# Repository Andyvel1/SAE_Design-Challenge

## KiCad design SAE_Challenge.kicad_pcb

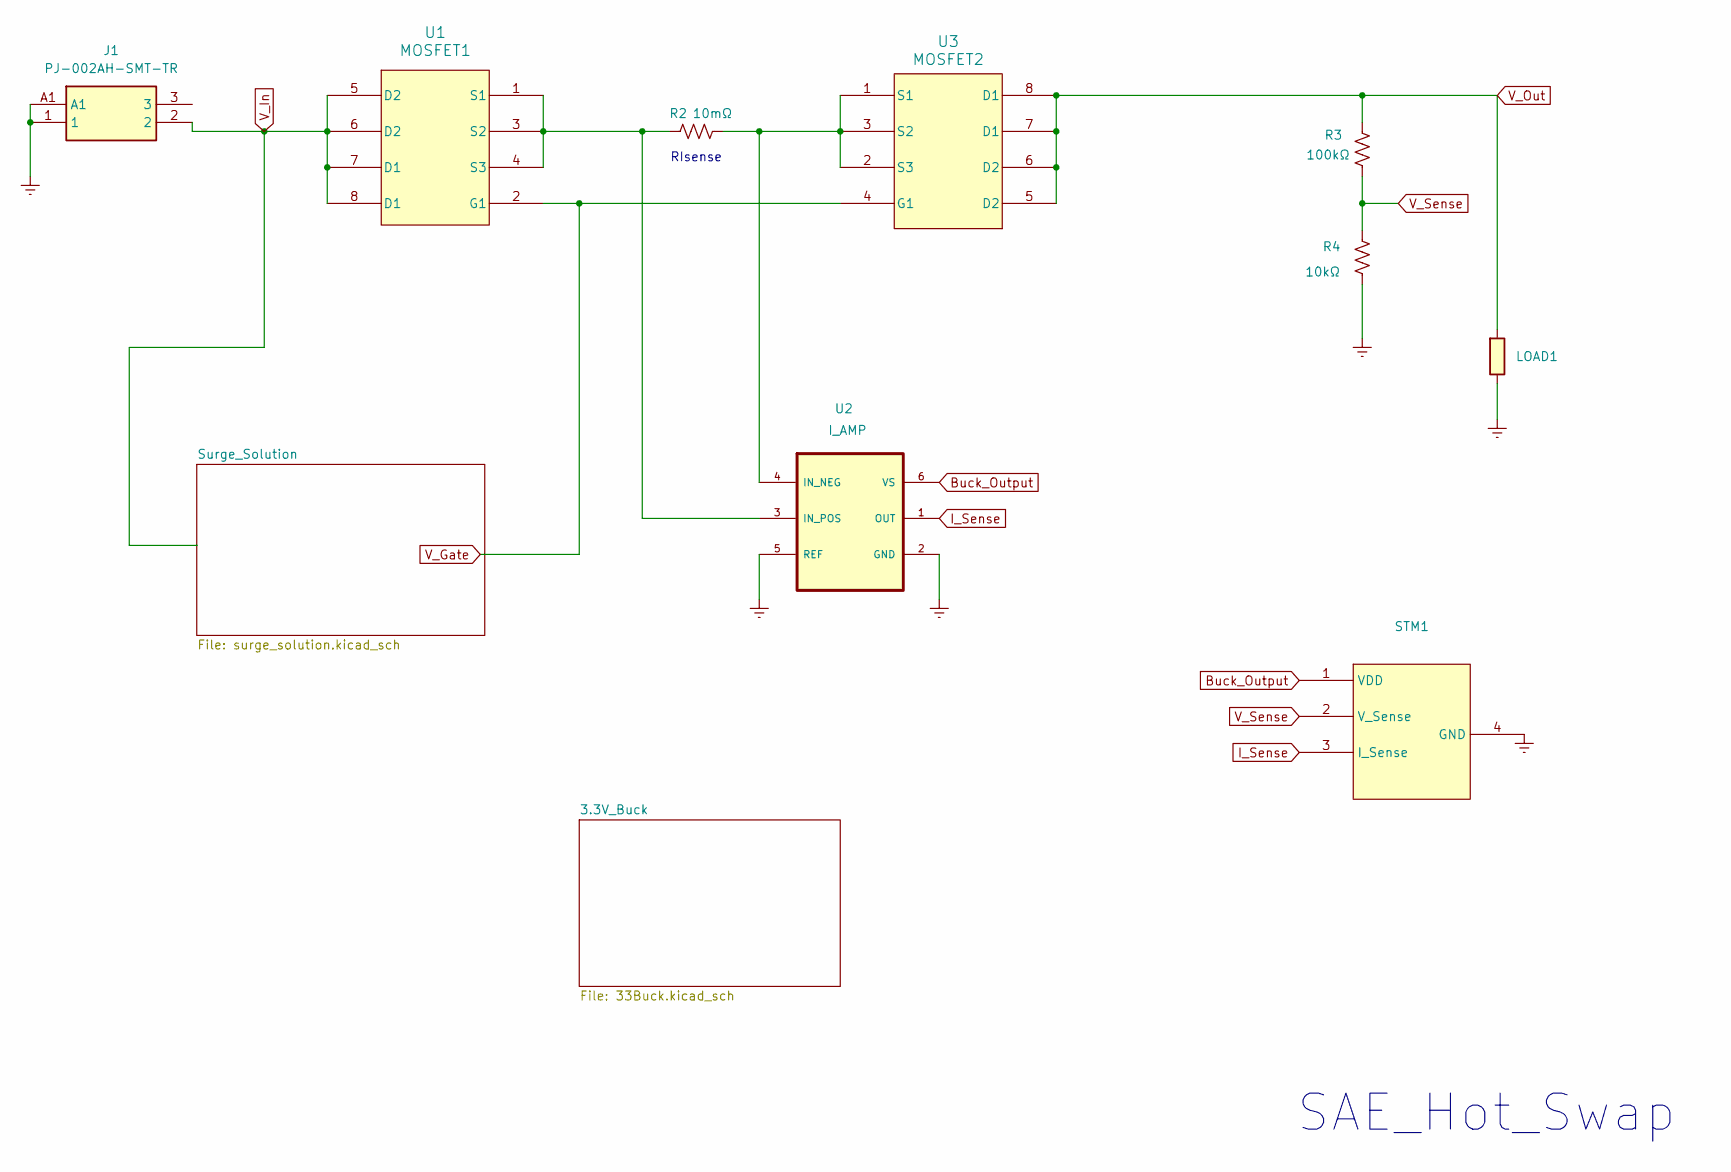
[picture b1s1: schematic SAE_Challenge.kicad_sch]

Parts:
J1: PJ-002AH-SMT-TR; PJ002AHSMTTR; Manufacturer_Part_Number PJ-002AH-SMT-TR; Mouser Part Number 490-PJ-002AH-SMT-TR
LOAD1: R
R2: 10mΩ; RES_RL2512_6P35X3P2_YAG
R3: 100kΩ; RESC1607X60N
R4: 10kΩ; RESC1607X60N
STM1: (no value)
U1: MOSFET1; SOIC-8_SI
U2: I_AMP; SOT95P280X145-6N
U3: MOSFET2; SOIC-8_SI

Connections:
Buck_Output: STM1.1 (VDD), U2.6 (VS); also elsewhere on the board
GNDREF: J1.1, J1.A1, LOAD1.2, R4.1, STM1.4 (GND), U2.2 (GND), U2.5 (REF); also elsewhere on the board
I_Sense: STM1.3 (I_Sense), U2.1 (OUT)
unnamed: R2.1, U1.1 (S1), U1.3 (S2), U1.4 (S3), U2.3 (IN_POS)
unnamed: R2.2, U2.4 (IN_NEG), U3.1 (S1), U3.2 (S3), U3.3 (S2)
V_Gate: U1.2 (G1), U3.4 (G1); also elsewhere on the board
V_In: J1.2, U1.5 (D2), U1.6 (D2), U1.7 (D1), U1.8 (D1); also elsewhere on the board
V_Out: LOAD1.1, R3.2, U3.5 (D2), U3.6 (D2), U3.7 (D1), U3.8 (D1); also elsewhere on the board
V_Sense: R3.1, R4.2, STM1.2 (V_Sense)

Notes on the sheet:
SAE_Hot_Swap
RIsense

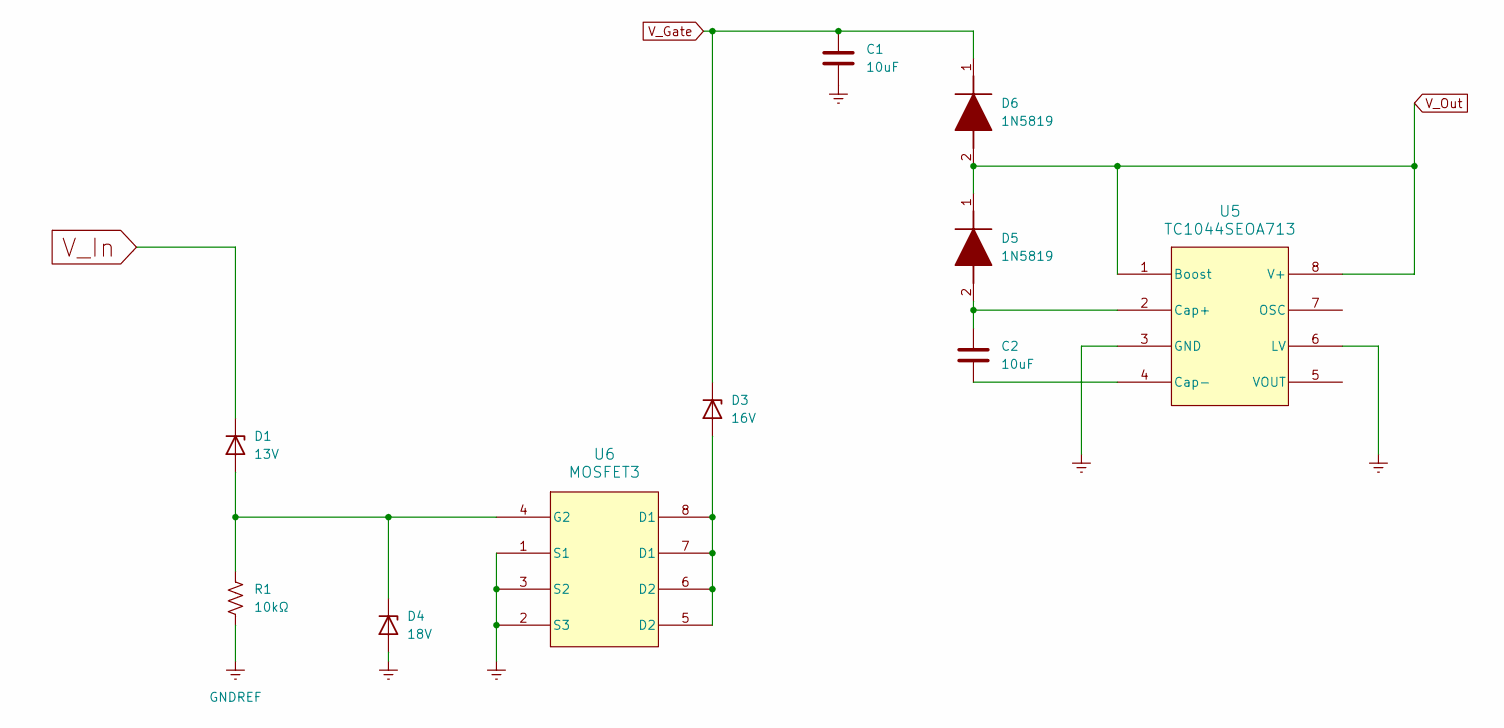
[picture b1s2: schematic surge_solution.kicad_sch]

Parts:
C1, C2: 10uF; CAPC2012X145N
D1: 13V; SOD3716X145N
D3: 16V; SOD3716X135N
D4: 18V; SOD-123_ONS
D5, D6: 1N5819; SMB_ONS; Manufacturer_Part_Number 1N5819; Mouser Part Number 821-1N5819
R1: 10kΩ; RESC1607X60N
U5: TC1044SEOA713; SOIC8-N_MC_MCH
U6: MOSFET3; SOIC-8_SI

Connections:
GNDREF: C1.2, D4.2 (A), R1.2, U5.3 (GND), U5.6 (LV), U6.1 (S1), U6.2 (S3), U6.3 (S2); also elsewhere on the board
unnamed: D1.2 (A), D4.1 (K), R1.1, U6.4 (G2)
unnamed: D3.2 (A), U6.5 (D2), U6.6 (D2), U6.7 (D1), U6.8 (D1)
unnamed: C2.1, D5.2 (A), U5.2 (Cap+)
unnamed: C2.2, U5.4 (Cap-)
V_Gate: C1.1, D3.1 (K), D6.1 (K); also elsewhere on the board
V_In: D1.1 (K); also elsewhere on the board
V_Out: D5.1 (K), D6.2 (A), U5.1 (Boost), U5.8 (V+); also elsewhere on the board

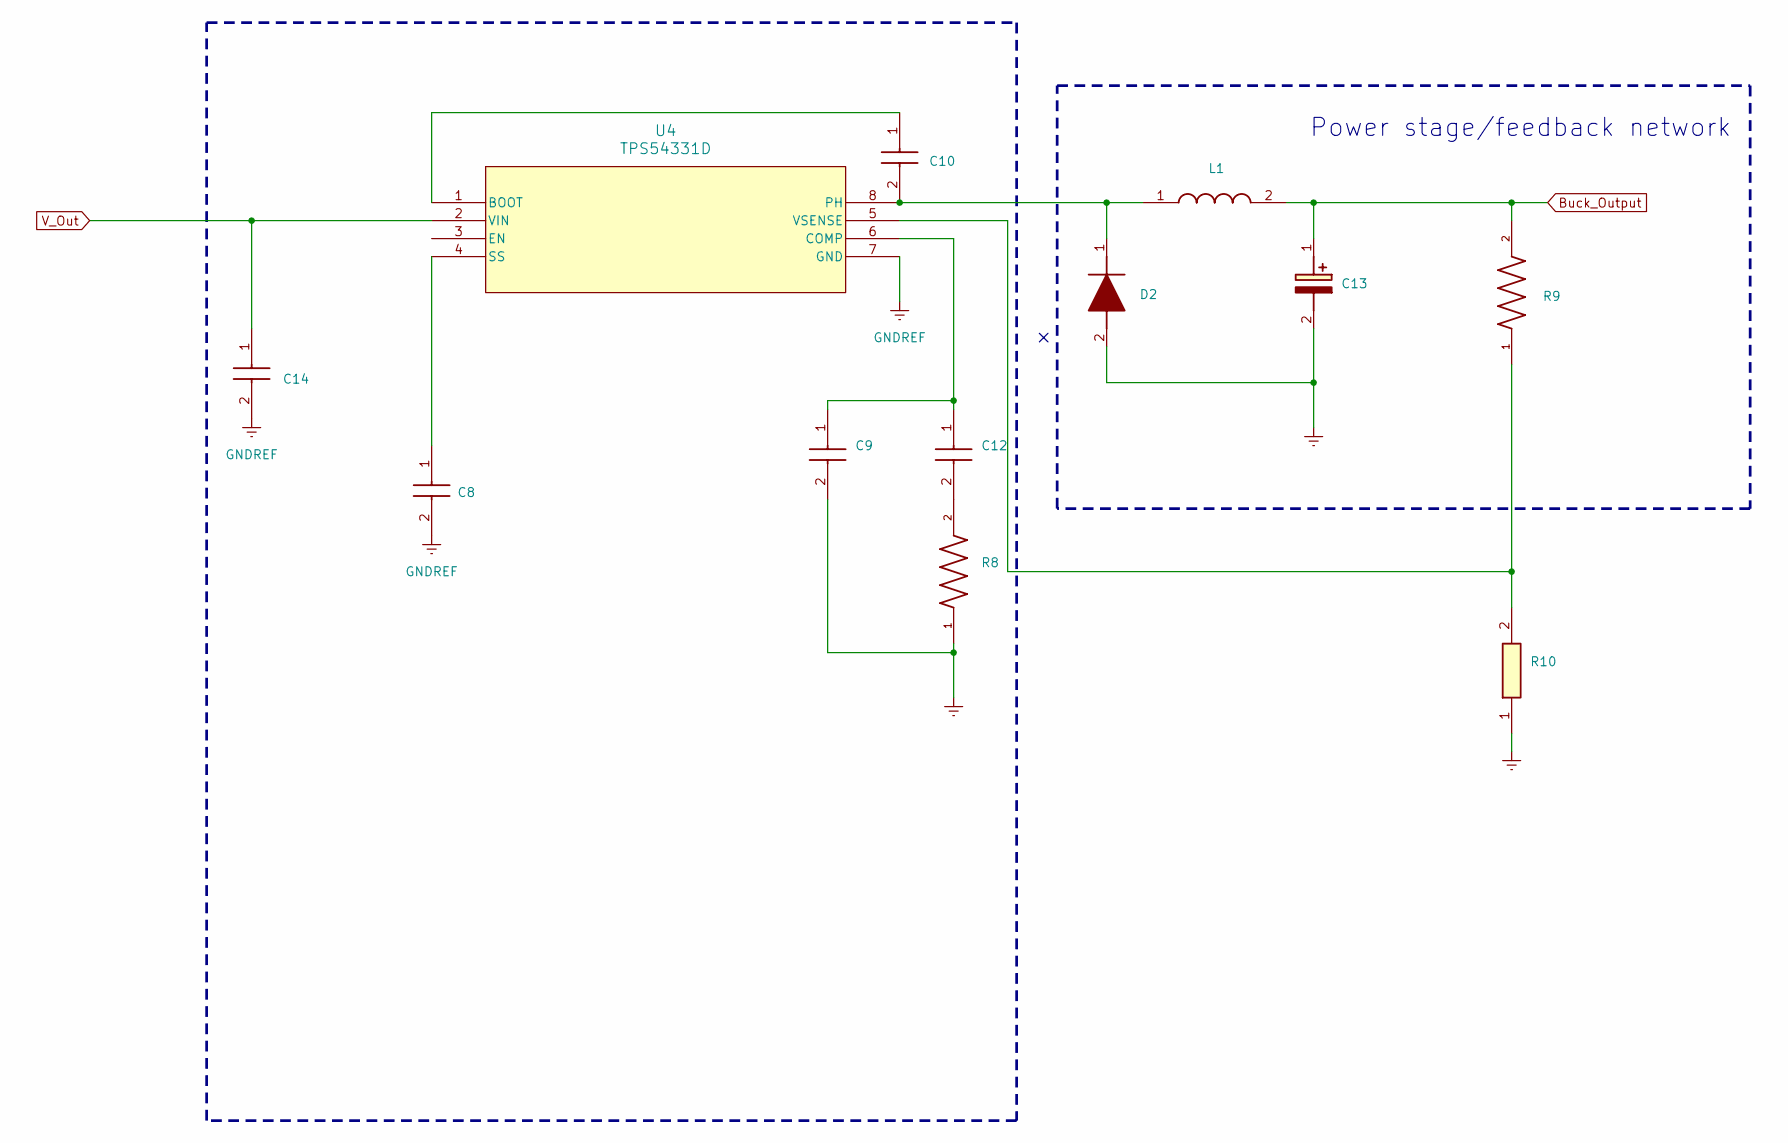
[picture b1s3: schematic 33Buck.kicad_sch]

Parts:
C8: CL10B103KB8NNNC; CAPC1608X90N; Manufacturer_Part_Number CL10B103KB8NNNC; Mouser Part Number 187-CL10B103KB8NNNC
C9: CL10C680JB8NNNC; CAPC1608X90N; Manufacturer_Part_Number CL10C680JB8NNNC; Mouser Part Number 187-CL10C680JB8NNNC
C10: CL10B104KB8NNNC; CAPC1608X90N; Manufacturer_Part_Number CL10B104KB8NNNC; Mouser Part Number 187-CL10B104KB8NNNC
C12: CL10B472KB8NNNC; CAPC1608X90N; Manufacturer_Part_Number CL10B472KB8NNNC; Mouser Part Number 187-CL10B472KB8NNNC
C13: TAJR475K010RNJ; CAPPM2014X120N; Manufacturer_Part_Number TAJR475K010RNJ; Mouser Part Number 581-TAJR475K010R
C14: CL21A106KAYNNNE; CAPC2012X145N; Manufacturer_Part_Number CL21A106KAYNNNE; Mouser Part Number 187-CL21A106KAYNNNE
D2: 1N5819; SMB_ONS; Manufacturer_Part_Number 1N5819; Mouser Part Number 821-1N5819
L1: SRN6045-470M; SRN6045_1; Manufacturer_Part_Number SRN6045-470M; Mouser Part Number 652-SRN6045-470M
R8, R9: RC0603FR-0731K6L; RC0603N_YAG
R10: RC0603FR-0710KL; RESC1608X55N; Manufacturer_Part_Number RC0603FR-0710KL; Mouser Part Number 603-RC0603FR-0710KL
U4: TPS54331D; D8

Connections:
Buck_Output: C13.1 (+), L1.2, R9.2; also elsewhere on the board
GNDREF: C8.2, C9.2, C13.2 (-), C14.2, D2.2 (A), R8.1, R10.1, U4.7 (GND); also elsewhere on the board
unnamed: C12.2, R8.2
unnamed: C10.2, D2.1 (K), L1.1, U4.8 (PH)
unnamed: C10.1, U4.1 (BOOT)
unnamed: C9.1, C12.1, U4.6 (COMP)
unnamed: C8.1, U4.4 (SS)
unnamed: R9.1, R10.2, U4.5 (VSENSE)
V_Out: C14.1, U4.2 (VIN); also elsewhere on the board

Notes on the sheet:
Power stage/feedback network

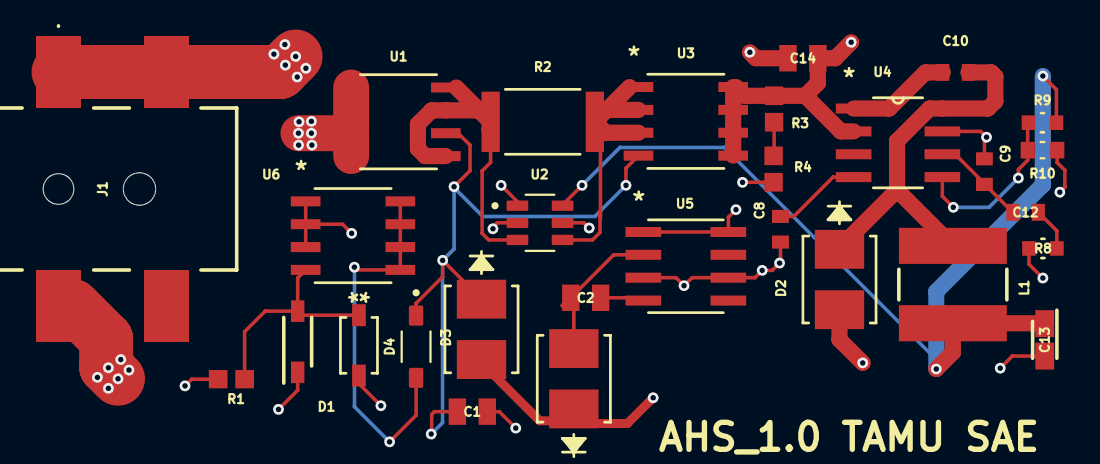
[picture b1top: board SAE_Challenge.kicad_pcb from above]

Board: 4 copper layers, 29 parts (0 on the bottom side), 18 nets.

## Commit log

2026-03-22 SAE Challenge surge protection circuit
